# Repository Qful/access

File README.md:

# [RFID](https://github.com/stops-top/RFID)

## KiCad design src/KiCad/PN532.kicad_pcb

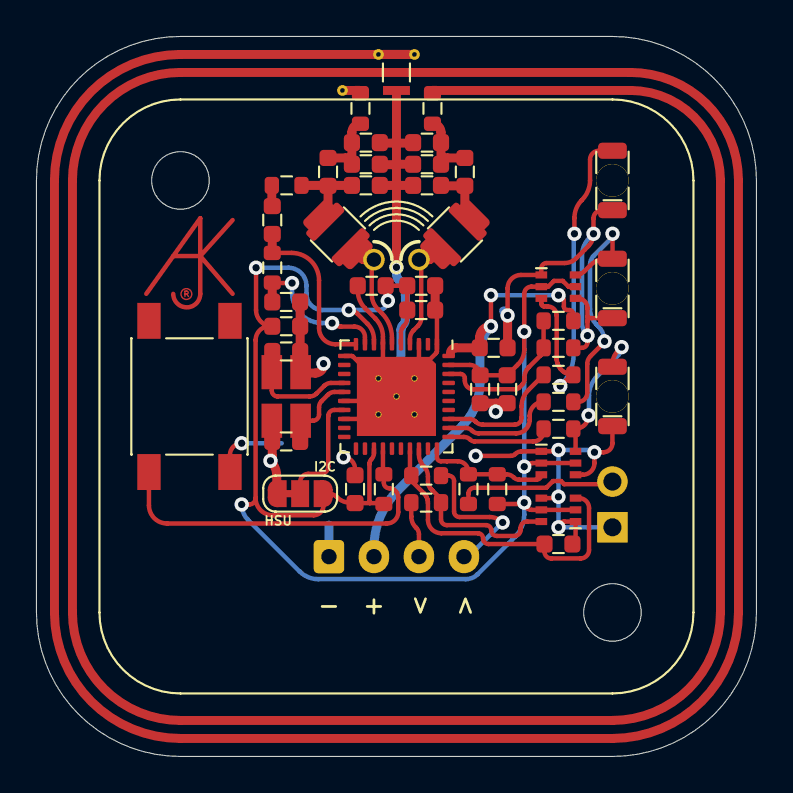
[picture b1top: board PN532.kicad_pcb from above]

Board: 2 copper layers, 40.0 x 40.0 mm, 53 parts (0 on the bottom side), 29 nets.

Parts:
A1: PN532-Antenna; PN532-Antenna5
AJK1: AJK
C1, C2: 160pF 1%; Cx2_0603
C3, C4: 22pF 1%; C_0603
C5, C6: 220pF; C_0603
C7, C9, C11, C12, C14, C18: 0.1uF; C_0603
C8: 1nF 2%; C_0603
C10, C13, C15: 4.7uF; C_0603
C16, C17: 22pF; C_0603
C19: 33pF; C_0603
D1: G; STP_156120xx7530
D2: A; STP_156120xx7530
D3: R; STP_156120xx7530
D4, D5, D6: BAV99S; SOT-363_SC-70-6
H1, H2: MountingHole; ISO7380-M3-NoPad
J1: Bell; PinHeader_1x02_P2.54mm_Vertical
J2: SPOX; Molex_MiniSPOX_H4V
JP1: I1; SolderJumper3
L1, L2: 560nH; L_1206_1008
R1, R2, R3: 0R; Hidden
R4: 2K7 1%; R_0603
R5: 1K 1%; R_0603
R6, R11, R15: 10K; R_0603
R7: 20K; R_0603
R8, R9, R10, R12, R13, R14: 100R; R_0603
SW1: TAMPER; SW_PUSH_6mm_SMD
TP1: TestPoint_2Pole; PN532-RF-Test
U1: PN532; QFN-40-1EP_6x6mm_P0.5mm_EP4.6x4.6mm
Y1: 27.12MHz; Crystal-3.4x2.7

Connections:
+3V3: C7.1, C10.1, C11.1, C12.1, C13.1, C15.1, C18.1, D4.2 (K2), D4.5 (K4), D5.2 (K2), D5.5 (K4), D6.2 (K2), D6.5 (K4), JP1.3 (B), R11.1, R15.1, U1.5 (TVDD), U1.8 (AVDD), U1.23 (PVDD), U1.39 (DVDD)
+5V: C14.1, J2.2, R6.2, U1.40 (VBAT)
GND: A1.2, C1.2, C2.1, C5.1, C6.1, C7.2, C9.2, C10.2, C11.2, C12.2, C13.2, C14.2, C15.2, C16.2, C17.2, C18.2, C19.2, D1.1 (K), D2.1 (K), D3.1 (K), D4.1 (A1), D4.4 (A3), D5.1 (A1), D5.4 (A3), D6.1 (A1), D6.4 (A3), J1.1, J2.1, JP1.1 (A), R7.2, SW1.1, U1.1 (DVSS), U1.3 (TVSS1), U1.7 (TVSS2), U1.11 (AVSS), U1.16 (I0), U1.18 (TESTEN), U1.41 (COPPER), Y1.2, Y1.4
unnamed: A1.1, C1.1, C3.2
unnamed: A1.3, C2.2, C4.1
unnamed: C3.1, C5.2, L1.2
unnamed: C4.2, C6.2, L2.1, R4.2
unnamed: C8.1, R5.1, U1.10 (RX)
unnamed: C8.2, R4.1
unnamed: C9.1, R5.2, U1.9 (VMID)
unnamed: C16.1, U1.14 (OSCIN), Y1.1
unnamed: C17.1, U1.15 (OSCOUT), Y1.3
unnamed: C19.1, D6.3 (K1A2), R14.2, U1.27 (NSS/P50_SCL/HSU_RX)
unnamed: D1.2 (A), D4.6 (K3A4), R8.2
unnamed: D2.2 (A), D5.6 (K3A4), R9.2
unnamed: D3.2 (A), D5.3 (K1A2), R10.2
unnamed: D4.3 (K1A2), R12.1, R15.2, U1.30 (SCK/P72)
unnamed: D6.6 (K3A4), R13.2, U1.28 (MOSI/SDA/HSU_TX)
unnamed: J1.2, R12.2
unnamed: J2.3, R13.1
unnamed: J2.4, R14.1
unnamed: JP1.2 (C), U1.17 (I1)
unnamed: L1.1, TP1.1, U1.4 (TX1)
unnamed: L2.2, TP1.2, U1.6 (TX2)
unnamed: R6.1, R7.1, U1.38 (RSTPD_N)
unnamed: R8.1, U1.31 (P31/DBG_TX)
unnamed: R9.1, U1.32 (P32_INT0)
unnamed: R10.1, U1.33 (P33_INT1)
unnamed: R11.2, SW1.2, U1.24 (P30/UART_RX)

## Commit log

2019-08-06 init
2019-08-15 fix v0.1.2
2019-08-16 fix test
2019-08-17 fix v0.1.3
2019-08-17 fix info
2019-08-17 fix v0.1.5
2019-08-18 fix for v0.2
2019-08-26 release v0.3
2020-04-19 del file
2022-03-02 some bug
2022-03-02 for risc-v
2022-03-04 add dev-kit
2022-03-04 test
2022-03-07 add otg
